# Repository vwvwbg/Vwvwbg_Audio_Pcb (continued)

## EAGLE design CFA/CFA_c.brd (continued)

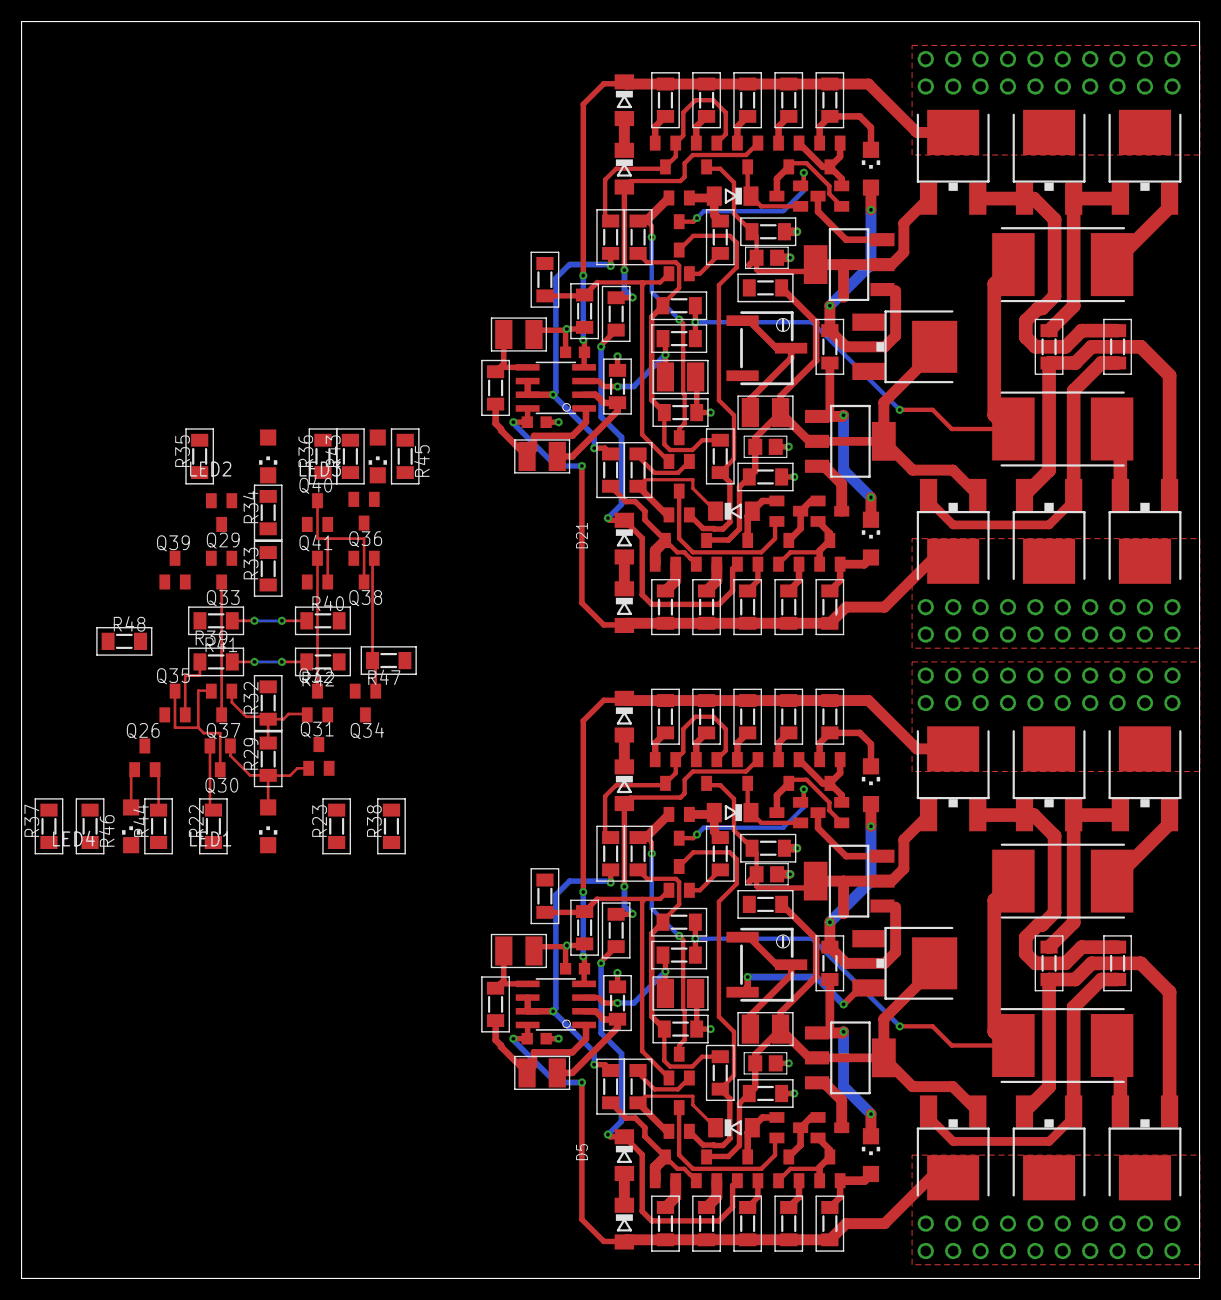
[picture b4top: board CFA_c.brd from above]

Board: 2 copper layers, 109.2 x 116.5 mm, 192 parts (0 on the bottom side), 133 nets.

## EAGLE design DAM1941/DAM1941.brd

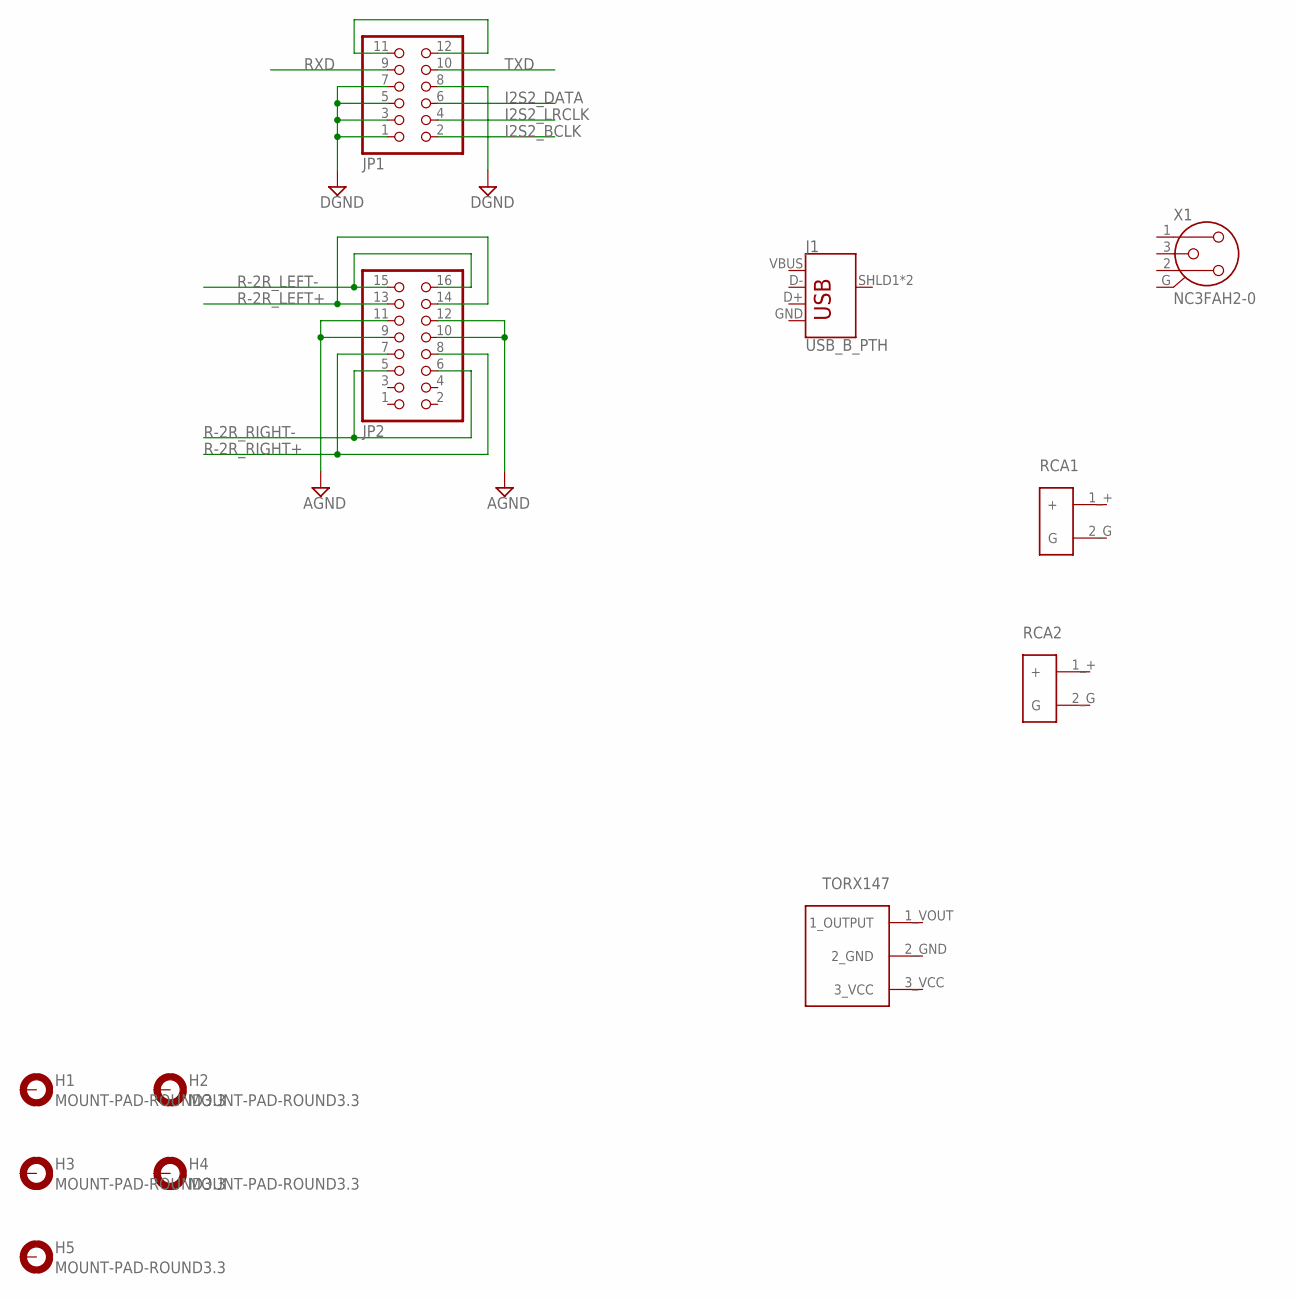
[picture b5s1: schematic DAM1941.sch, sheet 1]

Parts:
H1, H2, H3, H4, H5: MOUNT-PAD-ROUND3.3; 3,3-PAD
J1: USB_B_PTH; USB-B-PTH
JP1: PINHD-2X6/90; 2X06/90
JP2: PINHD-2X8/90; 2X08/90
RCA1, RCA2: RCA
U$1: TORX147
X1: NC3FAH2-0

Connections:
AGND: JP2.9, JP2.10, JP2.11, JP2.12; also elsewhere on the board
DGND: JP1.1, JP1.3, JP1.5, JP1.7, JP1.8; also elsewhere on the board
GND: J1.GND; also elsewhere on the board
I2S2_BCLK: JP1.2
I2S2_DATA: JP1.6
I2S2_LRCLK: JP1.4
unnamed: JP1.11, JP1.12
R-2R_LEFT+: JP2.13, JP2.14; also elsewhere on the board
R-2R_LEFT-: JP2.15, JP2.16; also elsewhere on the board
R-2R_RIGHT+: JP2.7, JP2.8; also elsewhere on the board
R-2R_RIGHT-: JP2.5, JP2.6; also elsewhere on the board
RXD: JP1.9; also elsewhere on the board
TXD: JP1.10; also elsewhere on the board
VBUS: J1.VBUS

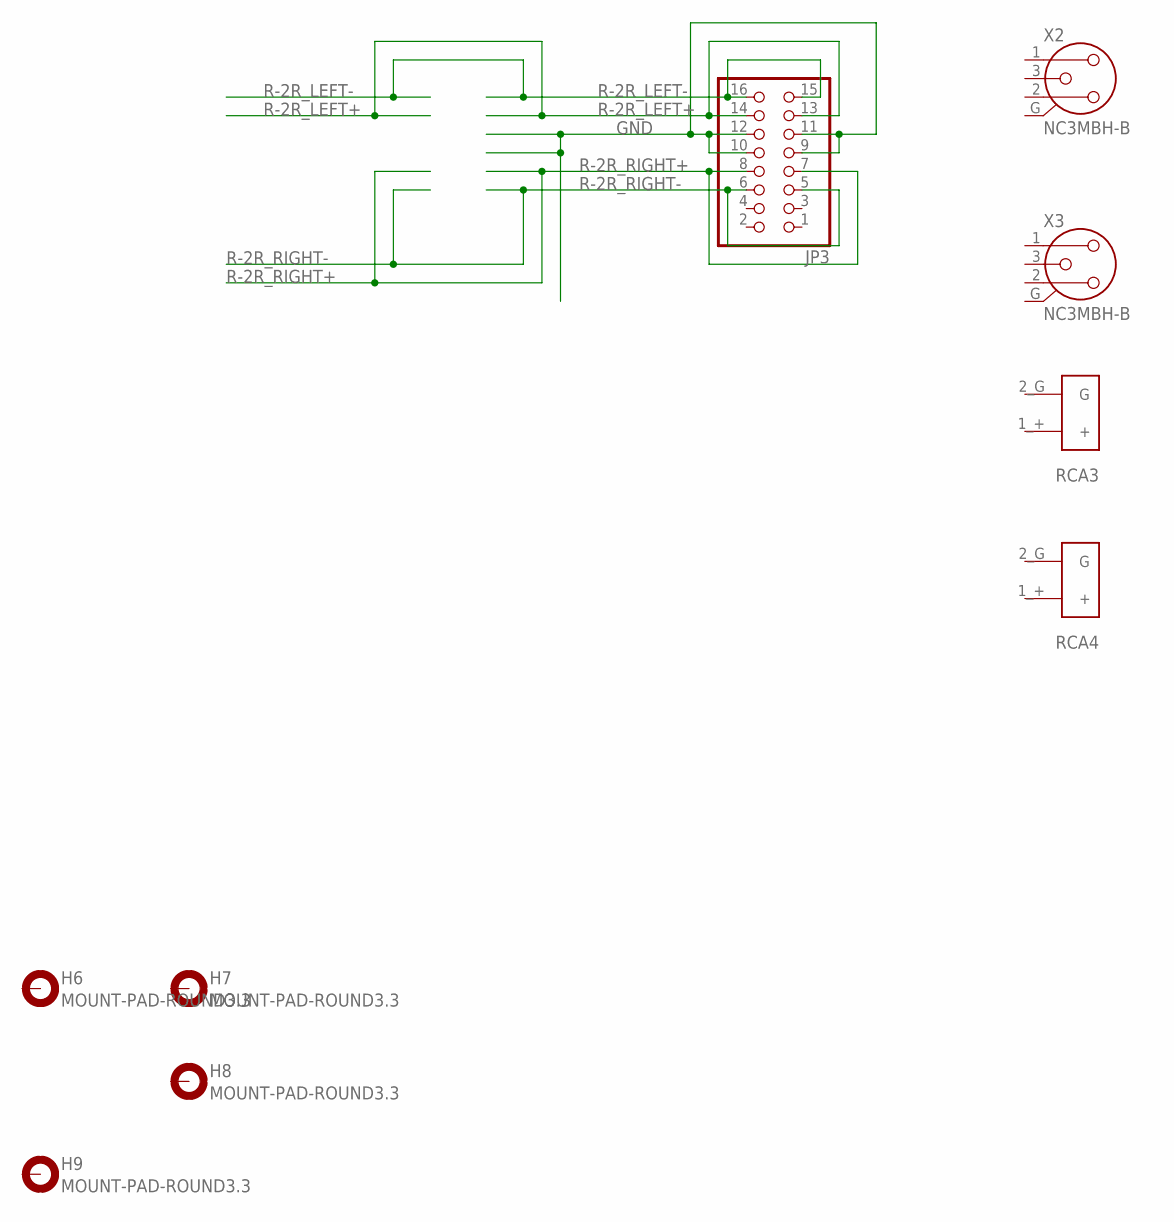
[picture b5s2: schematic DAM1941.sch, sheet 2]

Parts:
H6, H7, H8, H9: MOUNT-PAD-ROUND3.3; 3,3-PAD
JP3: PINHD-2X8; 2X08
RCA3, RCA4: RCA
X2, X3: NC3MBH-B

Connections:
GND: JP3.9, JP3.10, JP3.11, JP3.12; also elsewhere on the board
R-2R_LEFT+: JP3.13, JP3.14; also elsewhere on the board
R-2R_LEFT-: JP3.15, JP3.16; also elsewhere on the board
R-2R_RIGHT+: JP3.7, JP3.8; also elsewhere on the board
R-2R_RIGHT-: JP3.5, JP3.6; also elsewhere on the board

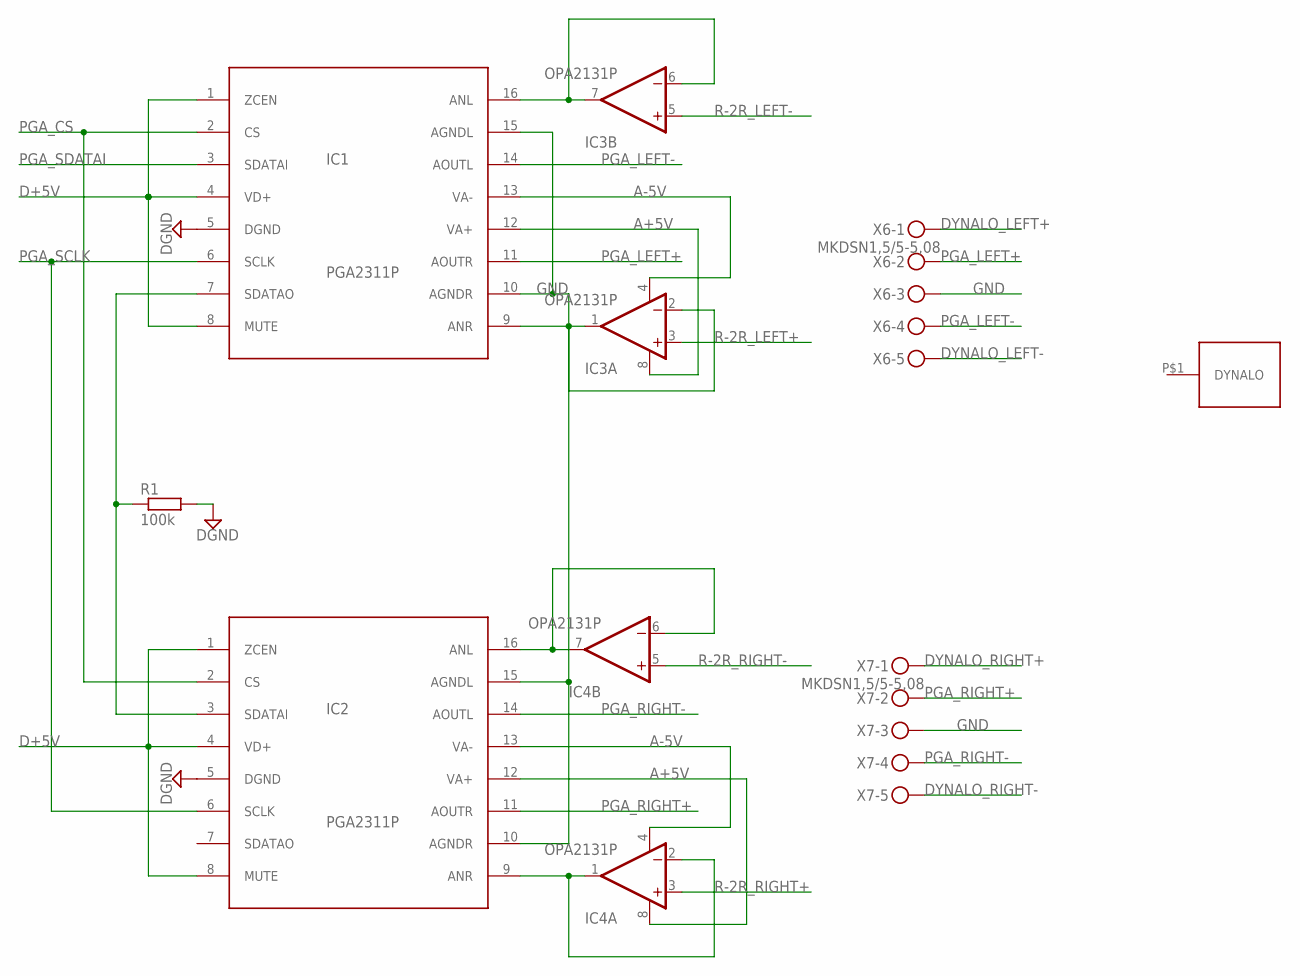
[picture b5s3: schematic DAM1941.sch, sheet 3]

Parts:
IC1, IC2: PGA2311P; DIL16
IC3, IC4: OPA2131P; DIL08
R1: 100k; MINI_MELF-0204R
U$3: DYNALO_DRILL; DYNALO17_DRILL
X6, X7: MKDSN1,5/5-5,08

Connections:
A+5V: IC1.12 (VA+), IC2.12 (VA+), IC3.8 (V+), IC4.8 (V+); also elsewhere on the board
A-5V: IC1.13 (VA-), IC2.13 (VA-), IC3.4 (V-), IC4.4 (V-); also elsewhere on the board
D+5V: IC1.1 (ZCEN), IC1.4 (VD+), IC1.8 (MUTE), IC2.1 (ZCEN), IC2.4 (VD+), IC2.8 (MUTE)
DGND: IC1.5 (DGND), IC2.5 (DGND), R1.2; also elsewhere on the board
DYNALO_LEFT+: X6.1; also elsewhere on the board
DYNALO_LEFT-: X6.5; also elsewhere on the board
DYNALO_RIGHT+: X7.1; also elsewhere on the board
DYNALO_RIGHT-: X7.5; also elsewhere on the board
GND: IC1.10 (AGNDR), IC1.15 (AGNDL), IC2.10 (AGNDR), IC2.15 (AGNDL), X6.3, X7.3; also elsewhere on the board
unnamed: IC2.9 (ANR), IC4.1 (OUT), IC4.2 (-IN)
unnamed: IC2.16 (ANL), IC4.6 (-IN), IC4.7 (OUT)
unnamed: IC1.9 (ANR), IC3.1 (OUT), IC3.2 (-IN)
unnamed: IC1.16 (ANL), IC3.6 (-IN), IC3.7 (OUT)
unnamed: IC1.7 (SDATAO), IC2.3 (SDATAI), R1.1
PGA_CS: IC1.2 (CS), IC2.2 (CS)
PGA_LEFT+: IC1.11 (AOUTR), X6.2
PGA_LEFT-: IC1.14 (AOUTL), X6.4
PGA_RIGHT+: IC2.11 (AOUTR), X7.2
PGA_RIGHT-: IC2.14 (AOUTL), X7.4
PGA_SCLK: IC1.6 (SCLK), IC2.6 (SCLK)
PGA_SDATAI: IC1.3 (SDATAI)
R-2R_LEFT+: IC3.3 (+IN); also elsewhere on the board
R-2R_LEFT-: IC3.5 (+IN); also elsewhere on the board
R-2R_RIGHT+: IC4.3 (+IN); also elsewhere on the board
R-2R_RIGHT-: IC4.5 (+IN); also elsewhere on the board

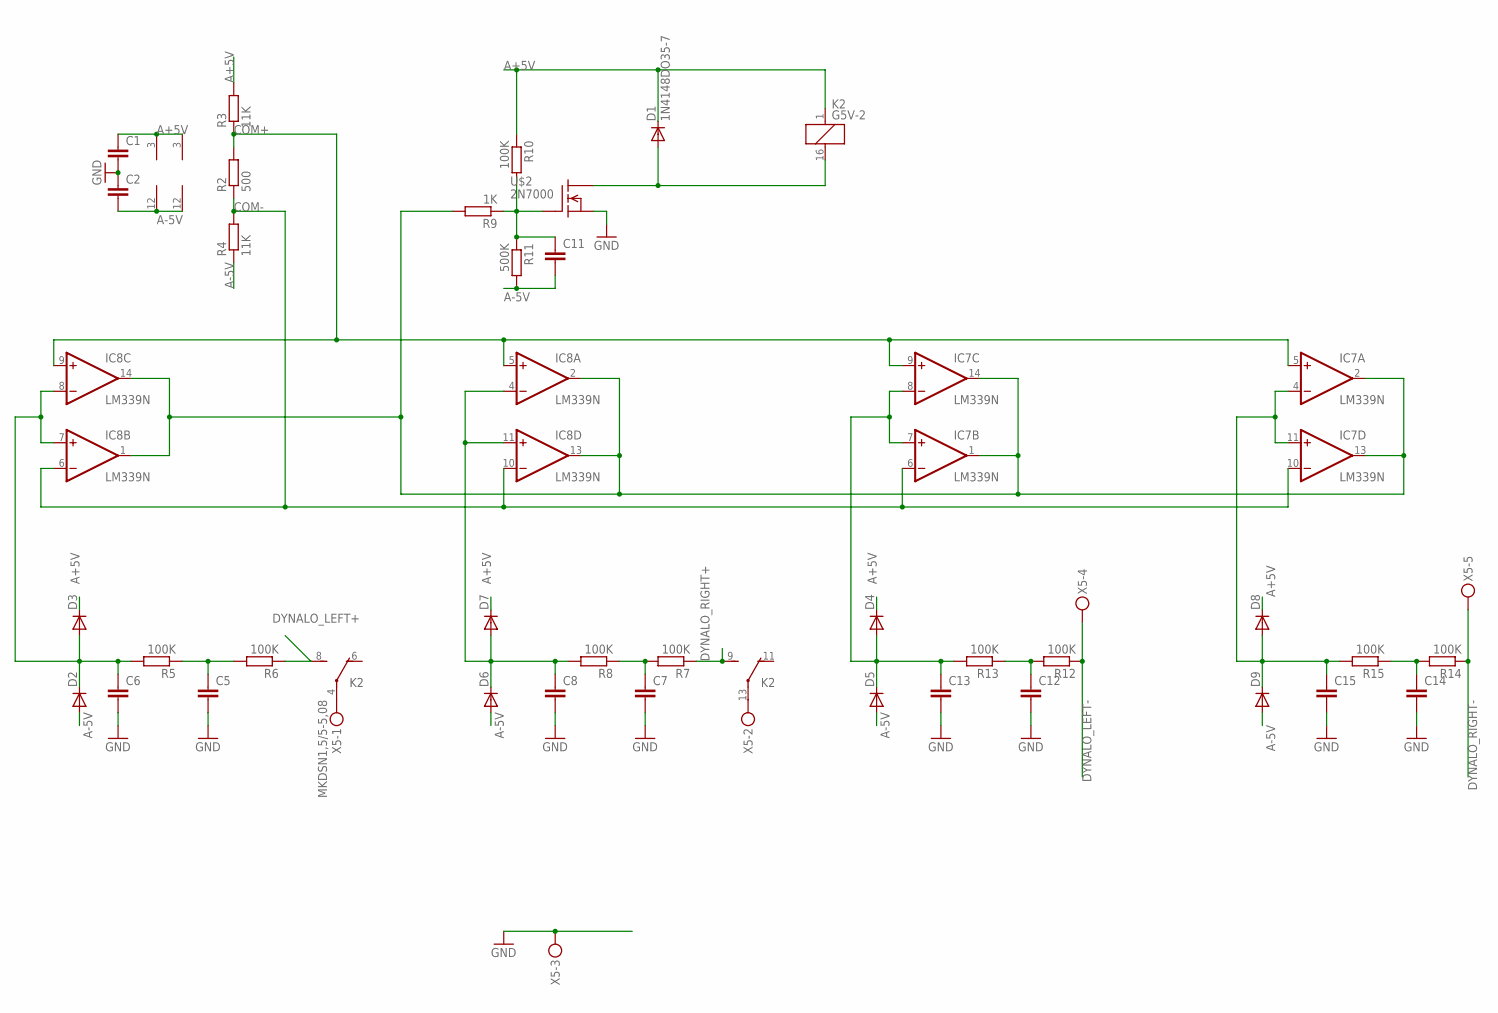
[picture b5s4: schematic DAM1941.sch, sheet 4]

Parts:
C1, C2, C5, C6, C7, C8, C11, C12, C13, C14, C15: C-EU050-024X044; C050-024X044
D1: 1N4148DO35-7; DO35-7
D2, D3, D4, D5, D6, D7, D8, D9: DIODE-D-5; D-5
IC7, IC8: LM339N; DIL14
K2: G5V-2
R2: 500; 0207/12
R3, R4: 11K; 0207/12
R5, R7, R8, R12, R13, R14, R15: 100K; 0207/5V
R6: 100K; 0207/10
R9: 1K; 0207/12
R10: 100K; 0207/12
R11: 500K; 0207/12
U$2: 2N7000; TO92-
X5: MKDSN1,5/5-5,08

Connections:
A+5V: C1.1, D1.C, D3.C, D4.C, D7.C, D8.C, IC7.3 (V+), IC8.3 (V+), K2.1, R3.2, R10.1; also elsewhere on the board
A-5V: C2.2, C11.2, D2.A, D5.A, D6.A, D9.A, IC7.12 (GND), IC8.12 (GND), R4.1, R11.2; also elsewhere on the board
COM+: IC7.5 (+IN), IC7.9 (+IN), IC8.5 (+IN), IC8.9 (+IN), R2.2, R3.1
COM-: IC7.6 (-IN), IC7.10 (-IN), IC8.6 (-IN), IC8.10 (-IN), R2.1, R4.2
DYNALO_LEFT+: K2.8 (S), R6.1; also elsewhere on the board
DYNALO_LEFT-: R12.1, X5.4; also elsewhere on the board
DYNALO_RIGHT+: K2.9 (S), R7.1; also elsewhere on the board
DYNALO_RIGHT-: R14.1, X5.5; also elsewhere on the board
GND: C1.2, C2.1, C5.2, C6.2, C7.2, C8.2, C12.2, C13.2, C14.2, C15.2, U$2.3 (S), X5.3; also elsewhere on the board
unnamed: C5.1, R5.1, R6.2
unnamed: C7.1, R7.2, R8.1
unnamed: C11.1, R9.1, R10.2, R11.1, U$2.2 (G)
unnamed: C6.1, D2.C, D3.A, IC8.7 (+IN), IC8.8 (-IN), R5.2
unnamed: C8.1, D6.C, D7.A, IC8.4 (-IN), IC8.11 (+IN), R8.2
unnamed: D1.A, K2.16 (2), U$2.1 (D)
unnamed: C13.1, D4.A, D5.C, IC7.7 (+IN), IC7.8 (-IN), R13.2
unnamed: C15.1, D8.A, D9.C, IC7.4 (-IN), IC7.11 (+IN), R15.2
unnamed: IC7.1 (OUT), IC7.2 (OUT), IC7.13 (OUT), IC7.14 (OUT), IC8.1 (OUT), IC8.2 (OUT), IC8.13 (OUT), IC8.14 (OUT), R9.2
unnamed: C12.1, R12.2, R13.1
unnamed: C14.1, R14.2, R15.1
unnamed: K2.13, X5.2
unnamed: K2.4, X5.1

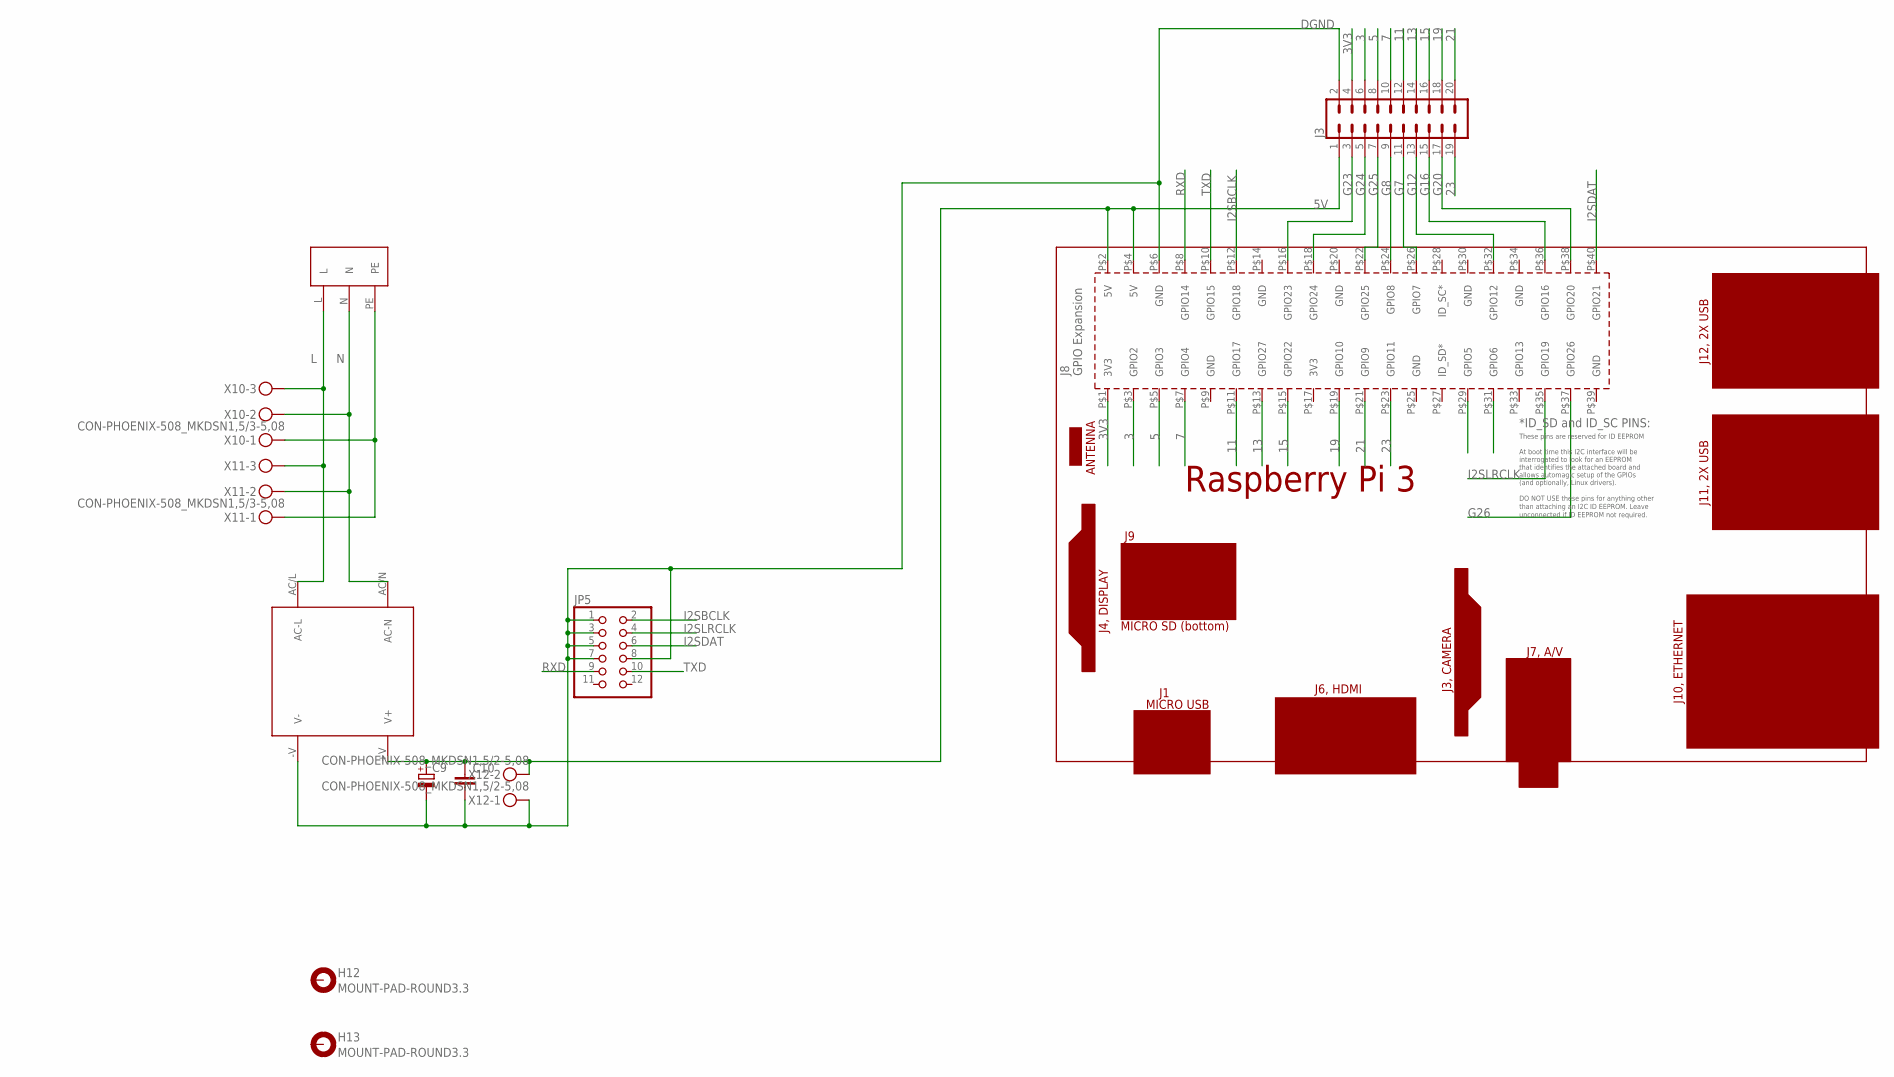
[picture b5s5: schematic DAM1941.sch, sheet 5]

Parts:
C9: CPOL-EUE5-8.5; E5-8,5
C10: C-EU050-050X075; C050-050X075
H12, H13: MOUNT-PAD-ROUND3.3; 3,3-PAD
J3: CONN_10X22X10_LOCK; 2X10_LOCK
JP5: PINHD-2X6; 2X06
PCB2: RPI3
U$5: DD21; DD21.NOCOVER
U$7: IRM-15-5; IRM-15
X10, X11: CON-PHOENIX-508_MKDSN1,5/3-5,08
X12: CON-PHOENIX-508_MKDSN1,5/2-5,08

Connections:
3: J3.6, PCB2.P$3 (GPIO2)
3V3: J3.4, PCB2.P$1 (3V3)
5: J3.8, PCB2.P$5 (GPIO3)
5V: C9.+, C10.1, J3.1, PCB2.P$2 (5V), PCB2.P$4 (5V), U$7.+V (V+), X12.2
7: J3.10, PCB2.P$7 (GPIO4)
11: J3.12, PCB2.P$11 (GPIO17)
13: J3.14, PCB2.P$13 (GPIO27)
15: J3.16, PCB2.P$15 (GPIO22)
19: J3.18, PCB2.P$19 (GPIO10)
21: J3.20, PCB2.P$21 (GPIO9)
23: J3.19, PCB2.P$23 (GPIO11)
DGND: C9.-, C10.2, J3.2, JP5.1, JP5.3, JP5.5, JP5.7, JP5.8, PCB2.P$6 (GND), U$7.-V (V-), X12.1; also elsewhere on the board
G7: J3.11, PCB2.P$26 (GPIO7)
G8: J3.9, PCB2.P$24 (GPIO8)
G12: J3.13, PCB2.P$32 (GPIO12)
G16: J3.15, PCB2.P$36 (GPIO16)
G20: J3.17, PCB2.P$38 (GPIO20)
G23: J3.3, PCB2.P$16 (GPIO23)
G24: J3.5, PCB2.P$18 (GPIO24)
G25: J3.7, PCB2.P$22 (GPIO25)
G26: PCB2.P$37 (GPIO26)
I2SBCLK: JP5.2, PCB2.P$12 (GPIO18)
I2SDAT: JP5.6, PCB2.P$40 (GPIO21)
I2SLRCLK: JP5.4, PCB2.P$35 (GPIO19)
L: U$5.L, U$7.AC/L (AC-L), X10.3, X11.3
N: U$5.N, U$7.AC/N (AC-N), X10.2, X11.2
unnamed: U$5.PE, X10.1, X11.1
RXD: JP5.9, PCB2.P$8 (GPIO14); also elsewhere on the board
TXD: JP5.10, PCB2.P$10 (GPIO15); also elsewhere on the board

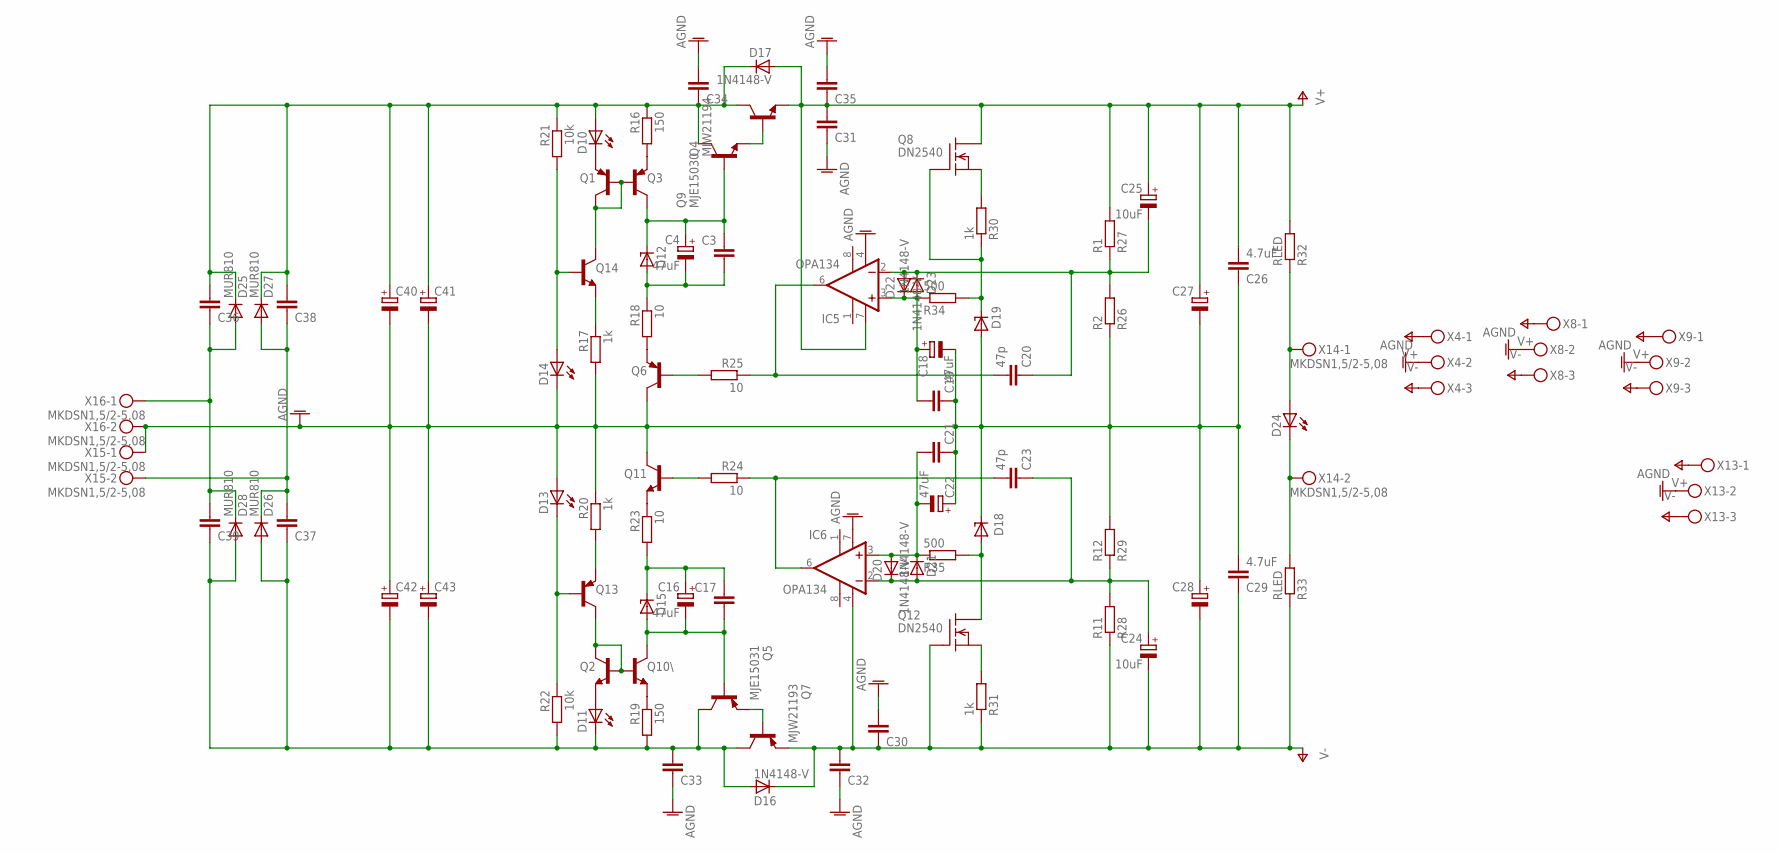
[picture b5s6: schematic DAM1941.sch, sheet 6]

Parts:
C3, C17, C19, C21, C30, C31, C32, C35, C36, C37, C38, C39: C-EU050-035X075; C050-035X075
C4, C16, C18, C22: 47uF; E5-8,5
C20, C23: 47p; C025_050-025X075
C24, C25: 10uF; E5-8,5
C26, C29: 4.7uF; C050-075X075
C27, C28, C40, C41, C42, C43: CPOL-EUE7.5-18; E7,5-18
C33, C34: C-EU050-075X075; C050-075X075
D10, D11, D13, D14, D24: LED5MM
D12, D15: 1N4728; DO41Z10
D16, D17, D20, D21, D22, D23: 1N4148-V; 1N4148
D18, D19: LT1021; DIL08
D25, D26, D27, D28: MUR810; TO220ACS
IC5, IC6: OPA134; DIL08
Q1, Q3, Q6, Q13: MPSA92-PNP-TO92-EBC; TO92-EBC
Q2, Q10\, Q11, Q14: MPSA42-NPN-TO92-EBC; TO92-EBC
Q4: MJW21194; TO-264
Q5: MJE15031; TO220KG
Q7: MJW21193; TO-264
Q8, Q12: DN2540; TO92-
Q9: MJE15030; TO220KG
R16, R19: 150; 0309/12
R17, R20, R30, R31: 1k; 0309/12
R18, R23, R24, R25: 10; 0309/12
R21, R22: 10k; 0309/12
R26: R2; 0309/12
R27: R1; 0309/12
R28: R11; 0309/12
R29: R12; 0309/12
R32, R33: RLED; 0309/12
R34, R35: 500; 0309/12
X4, X8, X9, X13: MKDSN1,5/3-5,08
X14, X15, X16: MKDSN1,5/2-5,08

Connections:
AGND: C18.-, C19.1, C21.1, C22.+, C26.1, C27.-, C28.+, C29.2, C30.2, C31.1, C32.1, C33.1, C34.2, C35.2, C40.-, C41.-, C42.+, C43.+, D13.A, D14.K (C), D18.6 (OUT), D19.4 (GND), IC5.4 (V-), IC6.7 (V+), Q6.C, Q11.C, R17.2, R20.1, R26.1, R29.2, X4.2, X8.2, X9.2, X13.2, X15.1, X16.2; also elsewhere on the board
unnamed: Q1.B, Q1.C, Q3.B, Q14.C
unnamed: D10.K (C), Q1.E
unnamed: Q3.E, R16.2
unnamed: C34.1, C36.2, C38.2, C40.+, C41.+, D10.A, D17.C, D25.C, D27.C, Q4.C, Q9.2 (C), R16.1, R21.1
unnamed: C3.1, C4.+, D12.C, Q3.C, Q9.1 (B)
unnamed: C3.2, C4.-, D12.A, R18.1
unnamed: Q6.E, R18.2
unnamed: Q14.E, R17.1
unnamed: D14.A, Q14.B, R21.2
unnamed: Q13.E, R20.2
unnamed: D13.K (C), Q13.B, R22.1
unnamed: Q11.E, R23.1
unnamed: C16.+, C17.1, D15.C, R23.2
unnamed: C16.-, C17.2, D15.A, Q5.1 (B), Q10\.C
unnamed: Q2.B, Q2.C, Q10\.B, Q13.C
unnamed: Q10\.E, R19.1
unnamed: D11.A, Q2.E
unnamed: Q5.3 (E), Q7.B
unnamed: Q4.B, Q9.3 (E)
unnamed: C20.2, C20.3 (2), IC5.6 (OUT), R25.1
unnamed: C23.2, C23.3 (2), IC6.6 (OUT), R24.1
unnamed: Q11.B, R24.2
unnamed: Q6.B, R25.2
unnamed: C20.1, C25.-, D22.A, D23.C, IC5.2 (-IN), R26.2, R27.1
unnamed: D19.6 (OUT), Q8.2 (G), R30.1, R34.2
unnamed: C18.+, C19.2, D22.C, D23.A, IC5.3 (+IN), R34.1
unnamed: C21.2, C22.-, D20.A, D21.C, IC6.3 (+IN), R35.1
unnamed: D18.4 (GND), Q12.1 (D), R35.2
unnamed: C23.1, C24.+, D20.C, D21.A, IC6.2 (-IN), R28.2, R29.1
unnamed: Q12.3 (S), R31.2
unnamed: Q8.3 (S), R30.2
unnamed: D24.K (C), R33.2, X14.2
unnamed: D24.A, R32.1, X14.1
unnamed: C33.2, C37.1, C39.1, C42.-, C43.-, D11.K (C), D16.A, D26.A, D28.A, Q5.2 (C), Q7.C, R19.2, R22.2
unnamed: C36.1, C39.2, D25.A, D28.C, X16.1
unnamed: C37.2, C38.1, D26.C, D27.A, X15.2
V+: C25.+, C26.2, C27.+, C31.2, C35.1, D17.A, IC5.7 (V+), Q4.E, Q8.1 (D), R27.2, R32.2, X4.1, X8.1, X9.1, X13.1
V-: C24.-, C28.-, C29.1, C30.1, C32.2, D16.C, IC6.4 (V-), Q7.E, Q12.2 (G), R28.1, R31.1, R33.1, X4.3, X8.3, X9.3, X13.3

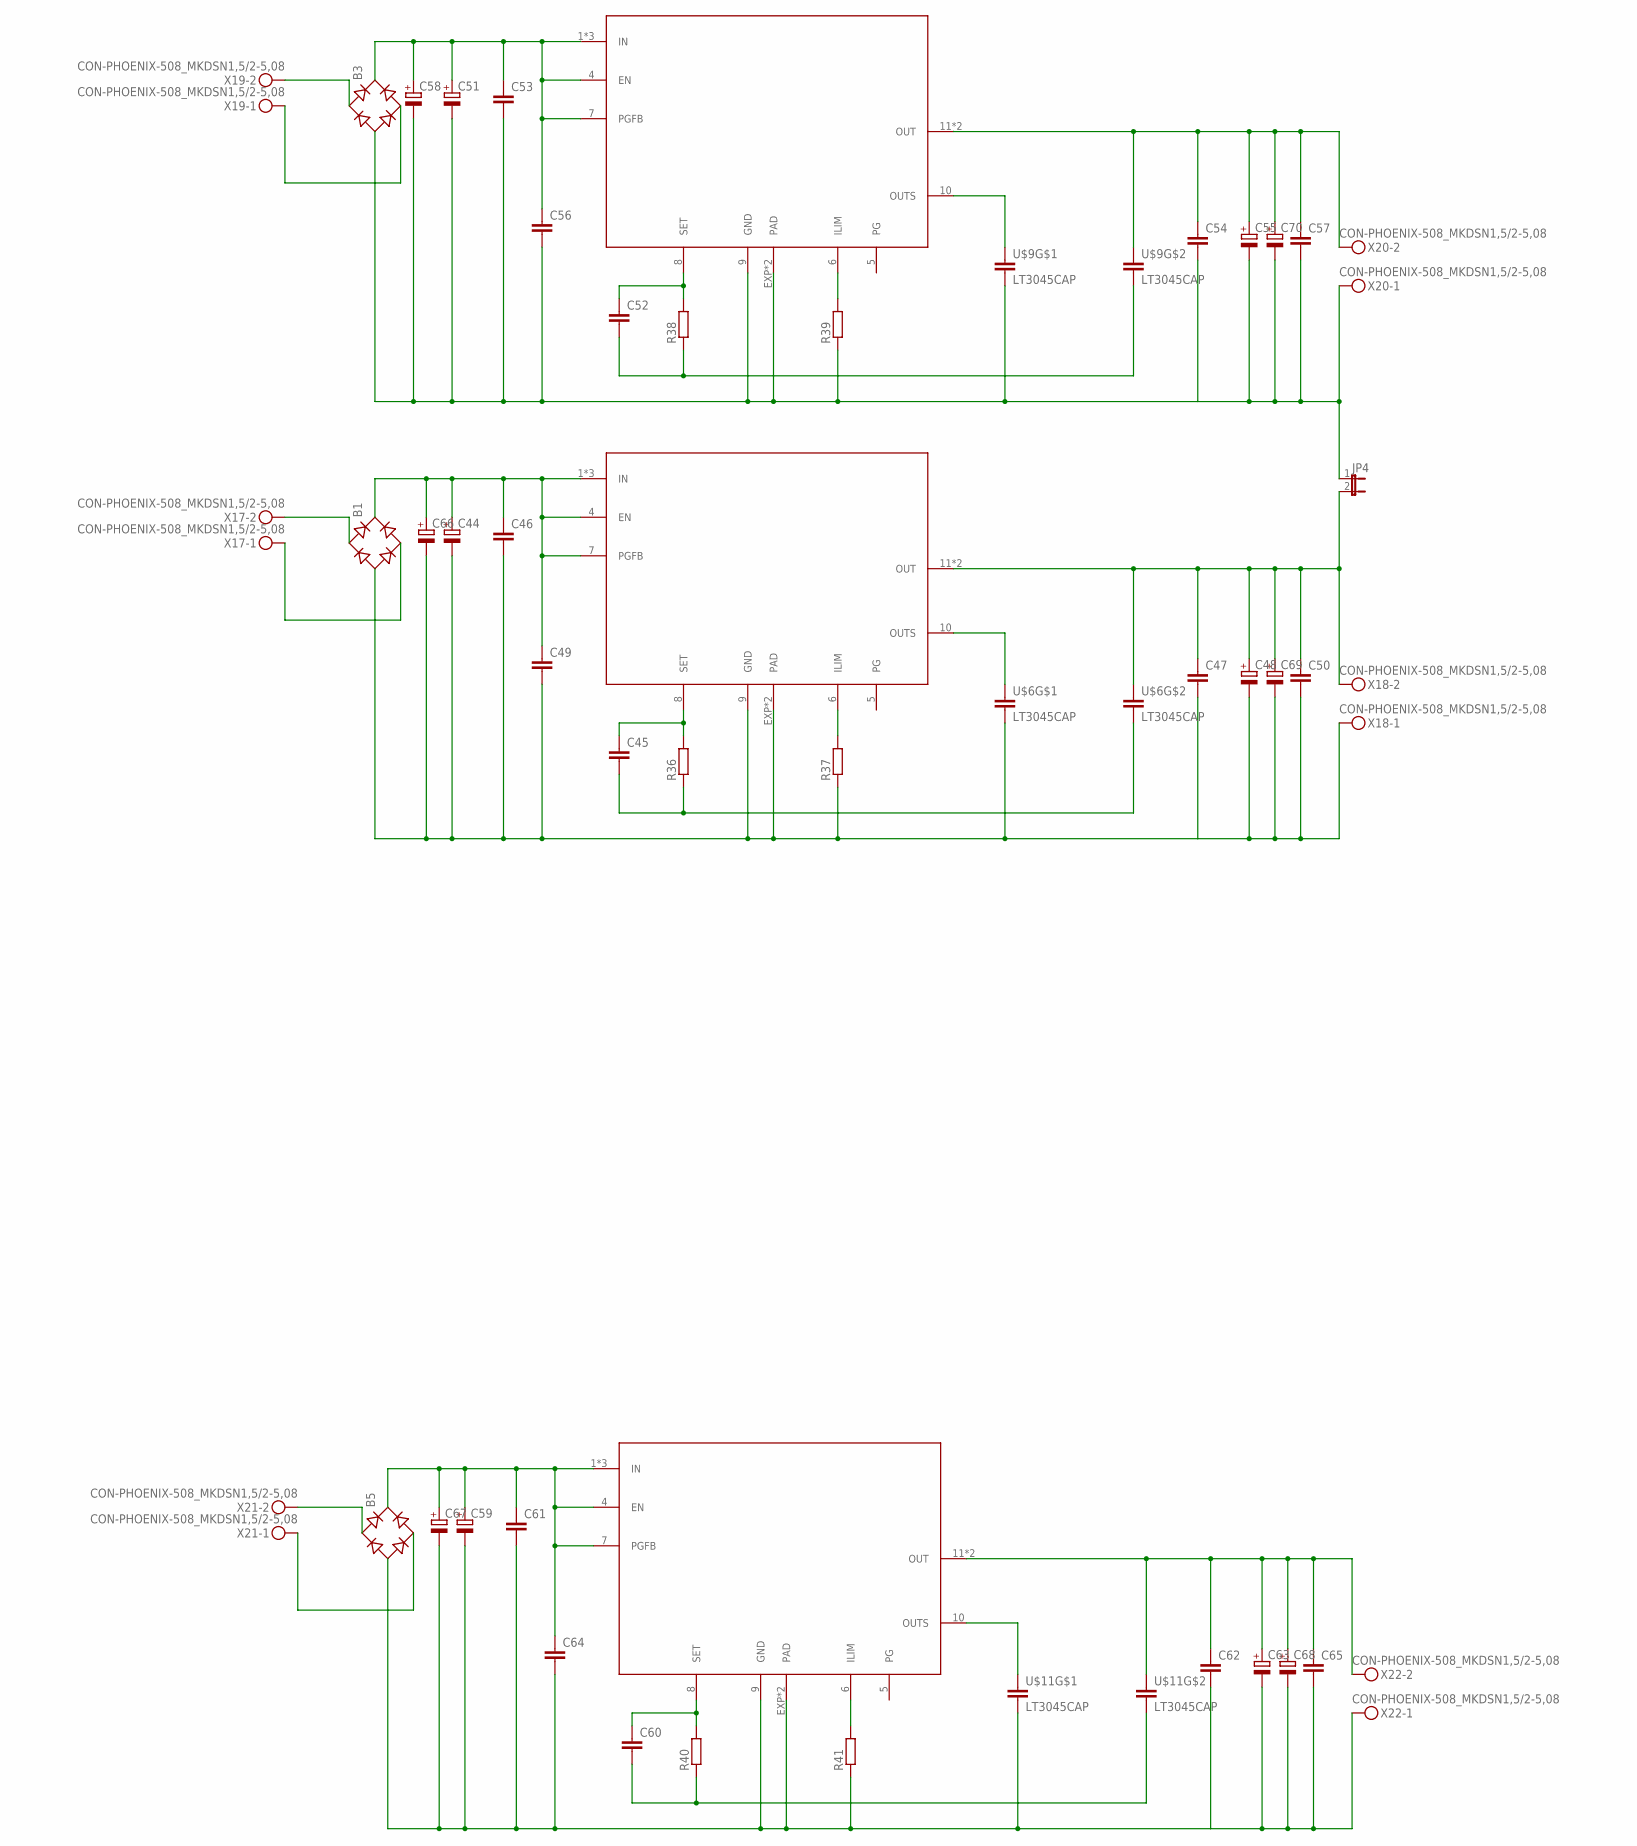
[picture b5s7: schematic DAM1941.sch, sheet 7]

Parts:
B1, B3, B5: RB1A
C44, C51, C59: CPOL-EUE7.5-18; E7,5-18
C45, C49, C50, C52, C56, C57, C60, C64, C65: C-EUC1206; C1206
C46, C47, C53, C54, C61, C62: C-EU050-050X075; C050-050X075
C48, C55, C63: CPOL-EUE5-10.5; E5-10,5
C58, C66, C67, C68, C69, C70: CPOL-EUSP-CAP-CX; SP-CAP-CX
JP4: JP1E; JP1
R36, R37, R38, R39, R40, R41: R-EU_MELF0204R; MINI_MELF-0204R
U$4, U$8, U$10: LT3045; MSOP12
U$6, U$9, U$11: LT3045CAP
X17, X18, X19, X20, X21, X22: CON-PHOENIX-508_MKDSN1,5/2-5,08

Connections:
GND1: B1.-, C44.-, C46.2, C47.2, C48.-, C49.2, C50.2, C66.-, C69.-, R37.1, U$4.9 (GND), U$4.EXP (PAD), U$4.EXP1 (PAD), U$6.5 (2), X18.1
GND2: B3.-, C51.-, C53.2, C54.2, C55.-, C56.2, C57.2, C58.-, C70.-, JP4.1, R39.1, U$8.9 (GND), U$8.EXP (PAD), U$8.EXP1 (PAD), U$9.5 (2), X20.1
GND3: B5.-, C59.-, C61.2, C62.2, C63.-, C64.2, C65.2, C67.-, C68.-, R41.1, U$10.9 (GND), U$10.EXP (PAD), U$10.EXP1 (PAD), U$11.5 (2), X22.1
IN1: B1.+, C44.+, C46.1, C49.1, C66.+, U$4.1 (IN), U$4.2 (IN), U$4.3 (IN), U$4.4 (EN), U$4.7 (PGFB)
IN2: B3.+, C51.+, C53.1, C56.1, C58.+, U$8.1 (IN), U$8.2 (IN), U$8.3 (IN), U$8.4 (EN), U$8.7 (PGFB)
IN3: B5.+, C59.+, C61.1, C64.1, C67.+, U$10.1 (IN), U$10.2 (IN), U$10.3 (IN), U$10.4 (EN), U$10.7 (PGFB)
unnamed: U$4.10 (OUTS), U$6.3 (1)
unnamed: R37.2, U$4.6 (ILIM)
unnamed: B1.AC2, X17.1
unnamed: B1.AC1, X17.2
unnamed: U$8.10 (OUTS), U$9.3 (1)
unnamed: R39.2, U$8.6 (ILIM)
unnamed: B3.AC2, X19.1
unnamed: B3.AC1, X19.2
unnamed: U$10.10 (OUTS), U$11.3 (1)
unnamed: R41.2, U$10.6 (ILIM)
unnamed: B5.AC2, X21.1
unnamed: B5.AC1, X21.2
OUT1: C47.1, C48.+, C50.1, C69.+, JP4.2, U$4.11 (OUT), U$4.12 (OUT), U$6.4 (1), X18.2
OUT2: C54.1, C55.+, C57.1, C70.+, U$8.11 (OUT), U$8.12 (OUT), U$9.4 (1), X20.2
OUT3: C62.1, C63.+, C65.1, C68.+, U$10.11 (OUT), U$10.12 (OUT), U$11.4 (1), X22.2
SET1: C45.1, R36.2, U$4.8 (SET)
SET2: C52.1, R38.2, U$8.8 (SET)
SET3: C60.1, R40.2, U$10.8 (SET)
SGND1: C45.2, R36.1, U$6.6 (2)
SGND2: C52.2, R38.1, U$9.6 (2)
SGND3: C60.2, R40.1, U$11.6 (2)
